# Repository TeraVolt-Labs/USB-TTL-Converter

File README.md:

# USB to TTL Converter — FT231XQ-R

A compact, reliable, and versatile **USB to UART** converter designed with the **FT231XQ-R** chipset. This open hardware project features dual voltage operation, UART activity LEDs, and dual JST-GH connectors to support a wide range of embedded development and debugging workflows.

---

## Features

- ✅ Based on **FTDI FT231XQ-R** (USB to UART bridge)
- ✅ **USB Type-C** connector for modern compatibility
- ✅ Selectable I/O voltage: **3.3V / 5V** via slider switch
- ✅ **TX/RX activity LEDs** for visual communication debug
- ✅ **Power LED** indicator
- ✅ Two **JST-GH** connectors:
  - **4-pin**: VCC, TX, RX, GND
  - **6-pin**: RST, RX, TX, VCC, CTS, GND
- ✅ Compact and easy to integrate
- 🔒 **Non-commercial Open Hardware License**

---

## 🔧 Specifications

| Parameter                 | Details                          |
|--------------------------|----------------------------------|
| USB Interface            | USB Type-C                       |
| USB-UART Chip            | FT231XQ-R                        |
| Logic Level              | Selectable 3.3V or 5V            |
| Status Indicators        | TX, RX, Power (LEDs)             |
| Connectors               | JST-GH 4-pin & 6-pin             |
| UART Signals             | TX, RX, CTS, RST                 |
| Board Size               | ~35mm × 25mm      |

---

## Pinouts

### 4-Pin JST-GH Connector

| Pin | Function | Description            |
|-----|----------|------------------------|
| 1   | VCC      | Selected voltage (3.3V/5V) |
| 2   | TX       | UART Transmit (from USB) |
| 3   | RX       | UART Receive (to USB)    |
| 4   | GND      | Ground                  |

### 6-Pin JST-GH Connector

| Pin | Function | Description           |
|-----|----------|-----------------------|
| 1   | RST      | Reset (active low)    |
| 2   | RX       | UART Receive          |
| 3   | TX       | UART Transmit         |
| 4   | VCC      | 3.3V or 5V (selected) |
| 5   | CTS      | Clear to Send         |
| 6   | GND      | Ground                |

---

## Driver Installation

### Windows

1. Download the VCP driver from: [https://ftdichip.com/drivers/](https://ftdichip.com/drivers/)
2. Install and plug in the device
3. COM port will appear in **Device Manager**

### macOS

- No driver required for modern versions
- Optional FTDI VCP driver available on FTDI website

### Linux

- Plug-and-play with most distributions
- Check with `dmesg | grep ttyUSB`

---

## License

**Custom Non-Commercial Open Hardware License**

> You are free to use, modify, reproduce, and distribute this hardware **for non-commercial purposes only**, provided that you give **proper credit** and include a copy of the license.

Full terms in [`LICENSE.txt`](./Licence.txt)

---

## Credits

Designed and developed by [TeraVolt Labs](https://www.linkedin.com/company/teravoltlabs)  
Powered by **FTDI FT231XQ-R**

---

## Support & Contributions

This is an open hardware project. Feel free to open issues, suggest improvements, or fork and build your own versions (non-commercially).

---

## Documentation
Official Documentation can be found at: [GitBook](https://teravolt.gitbook.io/teravolt/peripherals/usb-to-ttl-converter)

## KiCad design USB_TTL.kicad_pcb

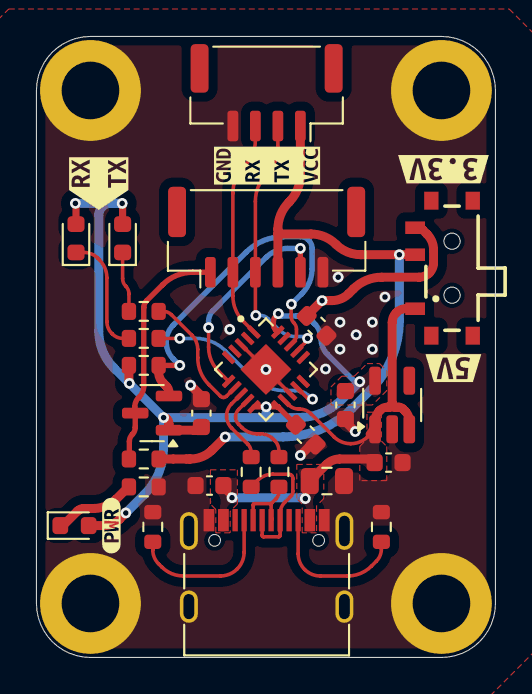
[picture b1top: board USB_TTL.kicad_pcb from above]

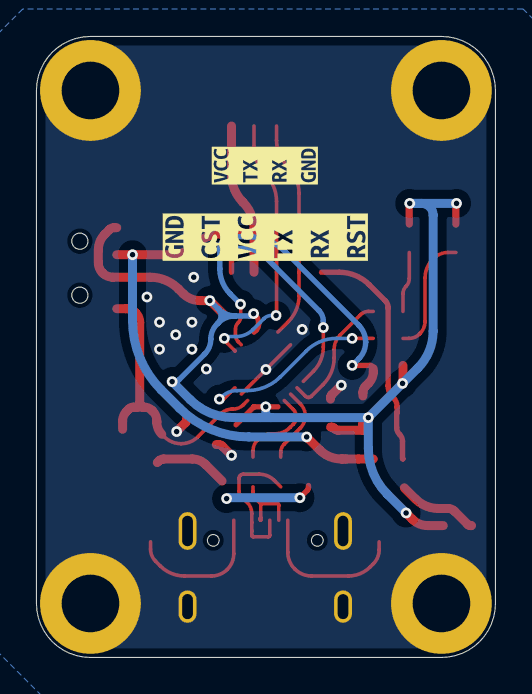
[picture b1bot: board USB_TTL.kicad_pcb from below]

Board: 2 copper layers, 25.5 x 34.5 mm, 37 parts (2 on the bottom side), 20 nets.

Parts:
C1: 0.1 uF; C_0603_1608Metric
C2, C4, C5, C6: 0.1uF; C_0603_1608Metric
C3: 10uF; C_0805_2012Metric
C7: 1.0uF; C_0603_1608Metric
D1, D2, D3: LED; LED_0603_1608Metric
H1, H2, H3, H4: MountingHole_Pad; MountingHole_3.2mm_M3_DIN965_Pad
J1: USB_C_Receptacle_USB2.0_16P; USB_C_Receptacle_G-Switch_GT-USB-7010ASV
J2: SM06B-GHS-TB; JST_GH_BM06B-GHS-TBT_1x06-1MP_P1.25mm_Vertical
J3: SM04B-GHS-TB_LF__SN_-; JST_GH_SM04B-GHS-TB_1x04-1MP_P1.25mm_Horizontal
Q1: 2N7002; SOT-23
R1, R2: 5.1K; R_0603_1608Metric
R3, R6: 10K; R_0603_1608Metric
R4, R5: 27R; R_0603_1608Metric
R7, R8, R9: 1K; R_0603_1608Metric
S1: 450404015514
U1: FT231XQ-R; QFN50P400X400X80-21N
U2: AP2112K-3.3; SOT-23-5_HandSoldering
kibuzzard-686110B6: G***; kibuzzard-686110B6
kibuzzard-686117B9: G***; kibuzzard-686117B9
kibuzzard-686117ED: G***; kibuzzard-686117ED
kibuzzard-68611096: G***; kibuzzard-68611096
kibuzzard-68611453: G***; kibuzzard-68611453
kibuzzard-68611696: G***; kibuzzard-68611696
kibuzzard-68611715: G***; kibuzzard-68611715

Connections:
+3.3V: C1.1, C4.1, C6.1, C7.1, D1.2 (A), D2.2 (A), D3.2 (A), Q1.1 (G), R3.1, S1.3, U1.10 (3V3OUT), U1.11 (RESET#), U1.20 (VCCIO), U2.5 (VOUT)
/CST: J2.5, U1.6 (CTS#)
/D+: J1.A6 (D+), J1.B6 (D+), R4.2
/D-: J1.A7 (D-), J1.B7 (D-), R5.1
/DM: R5.2, U1.9 (USBDM)
/DP: R4.1, U1.8 (USBDP)
/DTR: Q1.2 (S), R3.2, U1.18 (DTR#)
/RESET: J2.1, Q1.3 (D), R6.2
/RXLED: R7.1, U1.14 (CBUS1)
/Rx: J2.2, J3.3, U1.1 (RXD)
/TX: J2.3, J3.2, U1.17 (TXD)
/TXLED: R8.1, U1.7 (CBUS2)
GND: C1.2, C2.2, C3.2, C4.2, C5.2, C6.2, C7.2, H1.1, H2.1, H3.1, H4.1, J1.A1 (GND), J1.A12 (GND), J1.B1 (GND), J1.B12 (GND), J1.S1 (SHIELD), J2.6, J3.4, R1.1, R2.2, R9.1, U1.3 (GND), U1.13 (GND__1), U1.21 (GND__2), U2.2 (GND)
unnamed: D1.1 (K), R7.2
unnamed: D2.1 (K), R8.2
unnamed: D3.1 (K), R9.2
unnamed: J1.A5 (CC1), R2.1
unnamed: J1.B5 (CC2), R1.2
VBUS: C2.1, C3.1, C5.1, J1.A4 (VBUS), J1.A9 (VBUS), J1.B4 (VBUS), J1.B9 (VBUS), S1.1, U1.12 (VCC), U2.1 (VIN), U2.3 (EN)
VCC: J2.4, J3.1, R6.1, S1.2

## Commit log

2025-06-29 Upladed Project FIles
2025-06-29 Updated Licence File Path
